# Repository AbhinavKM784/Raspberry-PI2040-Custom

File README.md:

# Raspberry-PI2040-Custom

## Custom RP2040 Development Board

This project is a **custom-designed development board based on the Raspberry Pi RP2040 microcontroller**, built for embedded systems experimentation, firmware development, and learning PCB design. The board integrates the RP2040 dual-core ARM Cortex-M0+ microcontroller with carefully designed power management, USB connectivity, and accessible GPIO pins.

A key feature of the board is its **dual power capability**, allowing it to operate either from **USB power or a rechargeable battery source**. The power system includes a regulated **3.3 V supply**, proper decoupling, and power switching circuitry to ensure stable operation in both modes.

The PCB layout focuses on **good power integrity and signal routing practices**, including close placement of decoupling capacitors, controlled USB differential traces, and optimized trace widths for power delivery.

### Features

* **RP2040 dual-core ARM Cortex-M0+ microcontroller**
* **USB interface** for programming and communication
* **Battery-powered operation** for portable use
* **3.3 V regulated power supply**
* **Automatic or selectable power input (USB / battery)**
* **Exposed GPIO pins** for sensors and peripherals
* **Proper decoupling and power filtering**
* **Compact custom PCB layout**

### Purpose

This project is designed as a **learning and prototyping platform** for:

* Embedded firmware development
* Custom microcontroller board design
* Power management in portable electronics
* PCB layout and hardware debugging

---

---

---

------

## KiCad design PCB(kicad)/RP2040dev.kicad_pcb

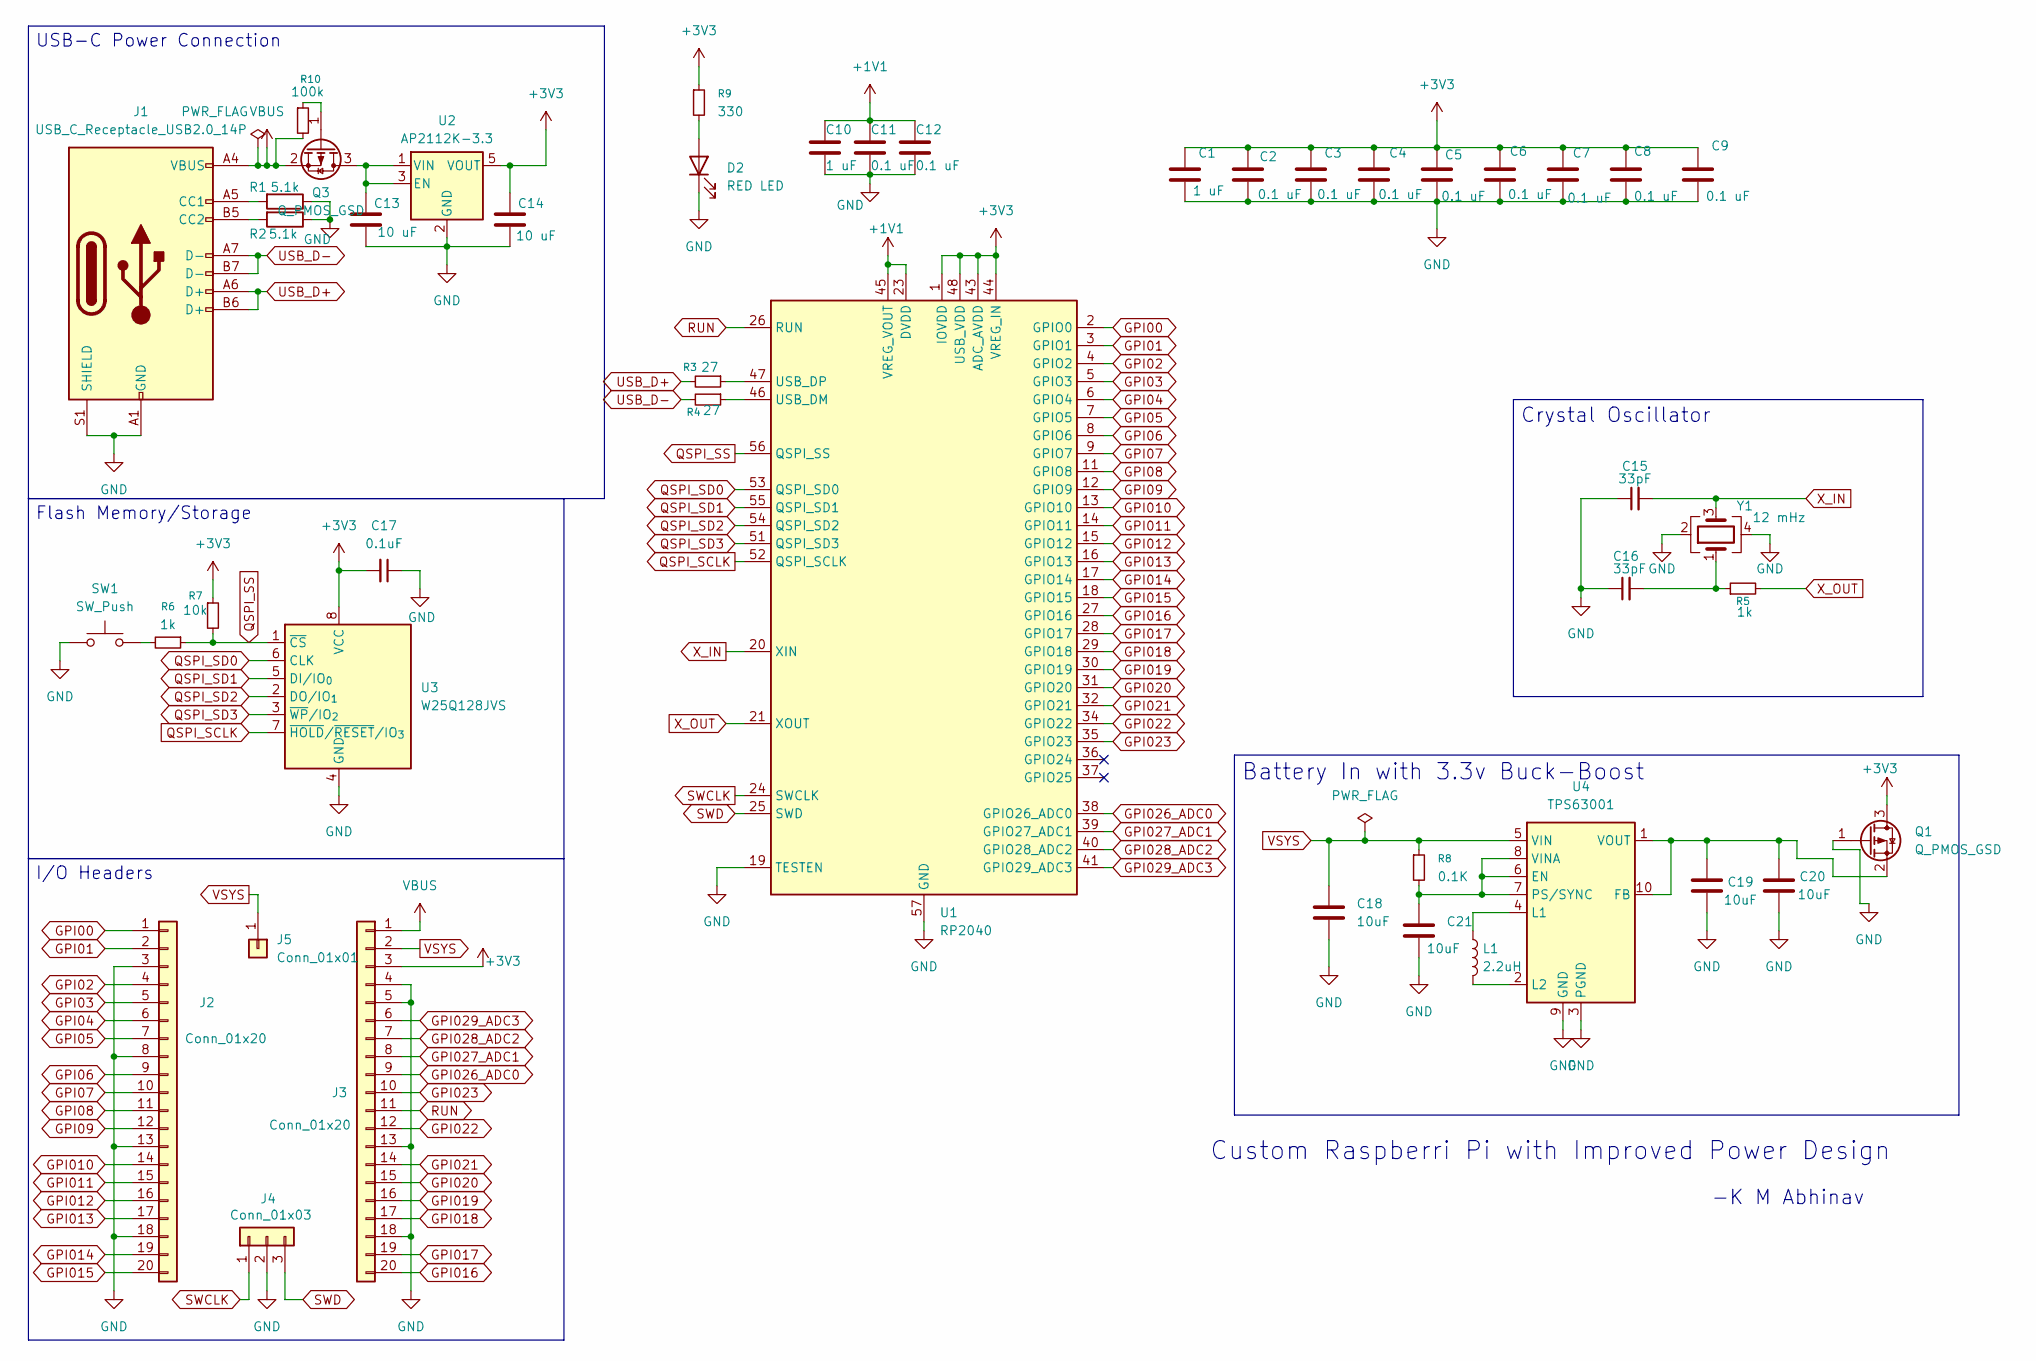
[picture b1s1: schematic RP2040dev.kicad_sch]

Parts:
C1, C10: 1 uF; C_0603_1608Metric
C2, C3, C4, C5, C6, C7, C8, C9, C11, C12: 0.1 uF; C_0603_1608Metric
C13, C14: 10 uF; C_0805_2012Metric
C15, C16: 33pF; C_0603_1608Metric
C17: 0.1uF; C_0603_1608Metric
C18, C19, C20, C21: 10uF; C_0805_2012Metric
D2: RED LED; LED_0805_2012Metric
J1: USB_C_Receptacle_USB2.0_14P; USB_C_Receptacle_HRO_TYPE-C-31-M-12
J2, J3: Conn_01x20; PinSocket_1x20_P2.54mm_Vertical
J4: Conn_01x03; PinSocket_1x03_P2.54mm_Vertical
J5: Conn_01x01; PinSocket_1x01_P2.54mm_Vertical
L1: 2.2uH; L_TDK_VLS6045EX_VLS6045AF
Q1, Q3: Q_PMOS_GSD; SOT-23
R1, R2: 5.1k; R_0603_1608Metric
R3, R4: 27; R_0603_1608Metric
R5, R6: 1k; R_0603_1608Metric
R7: 10k; R_0603_1608Metric
R8: 0.1K; R_0603_1608Metric
R9: 330; R_0603_1608Metric
R10: 100k; R_0603_1608Metric
SW1: SW_Push; SW_Push_SPST_NO_Alps_SKRK
U1: RP2040; QFN-56-1EP_7x7mm_P0.4mm_EP3.2x3.2mm
U2: AP2112K-3.3; SOT95P285X140-5N
U3: W25Q128JVS; Winbond_USON-8-1EP_3x2mm_P0.5mm_EP0.2x1.6mm
U4: TPS63001; Texas_DRC0010J_ThermalVias
Y1: 12 mHz; Crystal_SMD_3225-4Pin_3.2x2.5mm

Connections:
+1V1: C10.1, C11.1, C12.1, U1.23 (DVDD), U1.45 (VREG_VOUT), U1.50 (DVDD)
+3V3: C1.1, C2.1, C3.1, C4.1, C5.1, C6.1, C7.1, C8.1, C9.1, C14.1, C17.2, J3.3, Q1.3 (D), R7.1, R9.1, U1.1 (IOVDD), U1.10 (IOVDD), U1.22 (IOVDD), U1.33 (IOVDD), U1.42 (IOVDD), U1.43 (ADC_AVDD), U1.44 (VREG_IN), U1.48 (USB_VDD), U1.49 (IOVDD), U2.5 (VOUT), U3.8 (VCC)
GND: C1.2, C2.2, C3.2, C4.2, C5.2, C6.2, C7.2, C8.2, C9.2, C10.2, C11.2, C12.2, C13.2, C14.2, C15.1, C16.1, C17.1, C18.2, C19.2, C20.2, C21.2, D2.1 (K), J1.A1 (GND), J1.A12 (GND), J1.B1 (GND), J1.B12 (GND), J1.S1 (SHIELD), J2.3, J2.8, J2.13, J2.18, J3.4, J3.5, J3.13, J3.18, J4.2, Q1.1 (G), R1.1, R2.1, SW1.1, U1.19 (TESTEN), U1.57 (GND), U2.2 (GND), U3.4 (GND), U4.3 (PGND), U4.9 (GND), U4.11 (PGND), Y1.2, Y1.4
GPI00: J2.1, U1.2 (GPIO0)
GPI01: J2.2, U1.3 (GPIO1)
GPI02: J2.4, U1.4 (GPIO2)
GPI03: J2.5, U1.5 (GPIO3)
GPI04: J2.6, U1.6 (GPIO4)
GPI05: J2.7, U1.7 (GPIO5)
GPI06: J2.9, U1.8 (GPIO6)
GPI07: J2.10, U1.9 (GPIO7)
GPI08: J2.11, U1.11 (GPIO8)
GPI09: J2.12, U1.12 (GPIO9)
GPI010: J2.14, U1.13 (GPIO10)
GPI011: J2.15, U1.14 (GPIO11)
GPI012: J2.16, U1.15 (GPIO12)
GPI013: J2.17, U1.16 (GPIO13)
GPI014: J2.19, U1.17 (GPIO14)
GPI015: J2.20, U1.18 (GPIO15)
GPI016: J3.20, U1.27 (GPIO16)
GPI017: J3.19, U1.28 (GPIO17)
GPI018: J3.17, U1.29 (GPIO18)
GPI019: J3.16, U1.30 (GPIO19)
GPI020: J3.15, U1.31 (GPIO20)
GPI021: J3.14, U1.32 (GPIO21)
GPI022: J3.12, U1.34 (GPIO22)
GPI023: J3.10, U1.35 (GPIO23)
GPI026_ADC0: J3.9, U1.38 (GPIO26_ADC0)
GPI027_ADC1: J3.8, U1.39 (GPIO27_ADC1)
GPI028_ADC2: J3.7, U1.40 (GPIO28_ADC2)
GPI029_ADC3: J3.6, U1.41 (GPIO29_ADC3)
unnamed: C16.2, R5.1, Y1.1
unnamed: D2.2 (A), R9.2
unnamed: J1.A5 (CC1), R1.2
unnamed: J1.B5 (CC2), R2.2
unnamed: C19.1, C20.1, Q1.2 (S), U4.1 (VOUT), U4.10 (FB)
unnamed: C13.1, Q3.3 (D), U2.1 (VIN), U2.3 (EN)
unnamed: Q3.1 (G), R10.1
unnamed: R6.2, SW1.2
unnamed: R4.1, U1.46 (USB_DM)
unnamed: R3.1, U1.47 (USB_DP)
unnamed: C21.1, R8.2, U4.6 (EN), U4.7 (PS/SYNC), U4.8 (VINA)
unnamed: L1.1, U4.4 (L1)
unnamed: L1.2, U4.2 (L2)
QSPI_SCLK: U1.52 (QSPI_SCLK), U3.7 (~HOLD/~RESET/IO_{3})
QSPI_SD0: U1.53 (QSPI_SD0), U3.6 (CLK)
QSPI_SD1: U1.55 (QSPI_SD1), U3.5 (DI/IO_{0})
QSPI_SD2: U1.54 (QSPI_SD2), U3.2 (DO/IO_{1})
QSPI_SD3: U1.51 (QSPI_SD3), U3.3 (~WP/IO_{2})
QSPI_SS: R6.1, R7.2, U1.56 (QSPI_SS), U3.1 (~CS)
RUN: J3.11, U1.26 (RUN)
SWCLK: J4.1, U1.24 (SWCLK)
SWD: J4.3, U1.25 (SWD)
USB_D+: J1.A6 (D+), J1.B6 (D+), R3.2
USB_D-: J1.A7 (D-), J1.B7 (D-), R4.2
VBUS: J1.A4 (VBUS), J1.A9 (VBUS), J1.B4 (VBUS), J1.B9 (VBUS), J3.1, Q3.2 (S), R10.2
VSYS: C18.1, J3.2, J5.1, R8.1, U4.5 (VIN)
X_IN: C15.2, U1.20 (XIN), Y1.3
X_OUT: R5.2, U1.21 (XOUT)

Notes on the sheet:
-K M Abhinav
Custom Raspberri Pi with Improved Power Design
USB-C Power Connection
Battery In with 3.3v Buck-Boost
I/O Headers
Crystal Oscillator
Flash Memory/Storage

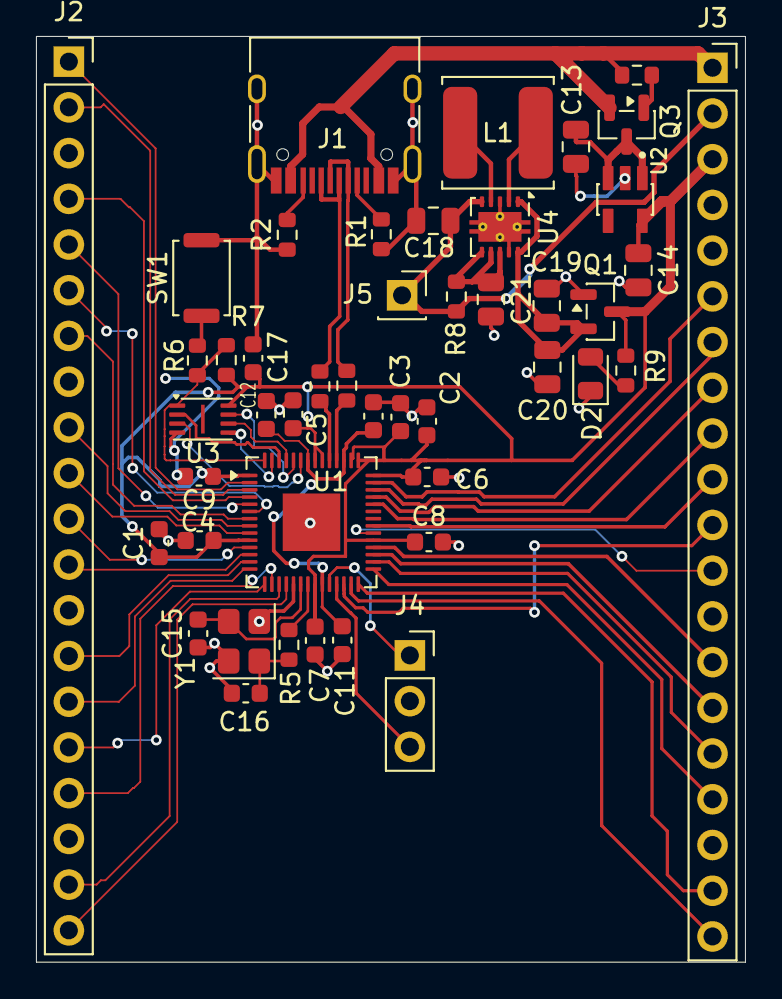
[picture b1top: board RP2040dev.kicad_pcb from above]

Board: 2 copper layers, 39.4 x 51.4 mm, 46 parts (0 on the bottom side), 59 nets.

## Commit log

2026-03-31 Create pre
2026-03-31 Create temp
